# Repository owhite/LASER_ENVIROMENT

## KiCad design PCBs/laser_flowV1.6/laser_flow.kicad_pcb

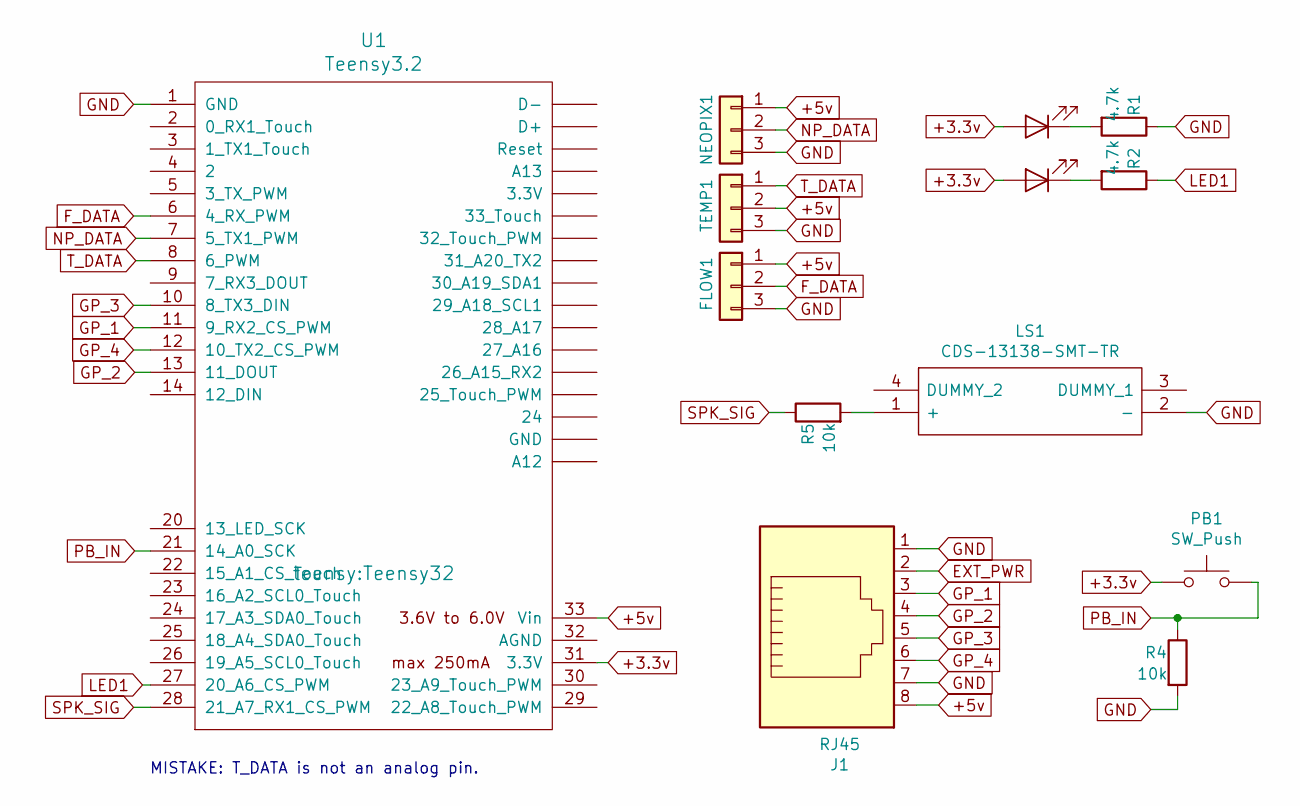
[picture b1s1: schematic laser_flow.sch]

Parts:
D1, D2: LED; LED_0805_2012Metric
FLOW1: Conn_01x03; PinHeader_1x03_P2.54mm_Vertical
J1: RJ45; my_RJ45_Amphenol
LS1: CDS-13138-SMT-TR; CDS13138SMTTR; Manufacturer_Part_Number CDS-13138-SMT-TR
NEOPIX1: Conn_01x03; PinHeader_1x03_P2.54mm_Vertical
PB1: SW_Push; SW_SPST_TL3342
R1, R2: 4.7k; R_0805_2012Metric
R4, R5: 10k; R_0805_2012Metric
TEMP1: Conn_01x03; PinHeader_1x03_P2.54mm_Vertical
U1: Teensy3.2; Teensy32

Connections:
+3.3v: D1.2 (A), D2.2 (A), PB1.1, U1.31 (3.3V)
+5v: FLOW1.1, J1.8, NEOPIX1.1, TEMP1.2, U1.33 (Vin)
EXT_PWR: J1.2
F_DATA: FLOW1.2, U1.6 (4_RX_PWM)
GND: FLOW1.3, J1.1, J1.7, LS1.2 (-), NEOPIX1.3, R1.1, R4.2, TEMP1.3, U1.1 (GND)
GP_1: J1.3, U1.11 (9_RX2_CS_PWM)
GP_2: J1.4, U1.13 (11_DOUT)
GP_3: J1.5, U1.10 (8_TX3_DIN)
GP_4: J1.6, U1.12 (10_TX2_CS_PWM)
LED1: R2.1, U1.27 (20_A6_CS_PWM)
NP_DATA: NEOPIX1.2, U1.7 (5_TX1_PWM)
unnamed: D1.1 (K), R1.2
unnamed: D2.1 (K), R2.2
unnamed: LS1.1 (+), R5.2
PB_IN: PB1.2, R4.1, U1.21 (14_A0_SCK)
SPK_SIG: R5.1, U1.28 (21_A7_RX1_CS_PWM)
T_DATA: TEMP1.1, U1.8 (6_PWM)

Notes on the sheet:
MISTAKE: T_DATA is not an analog pin.

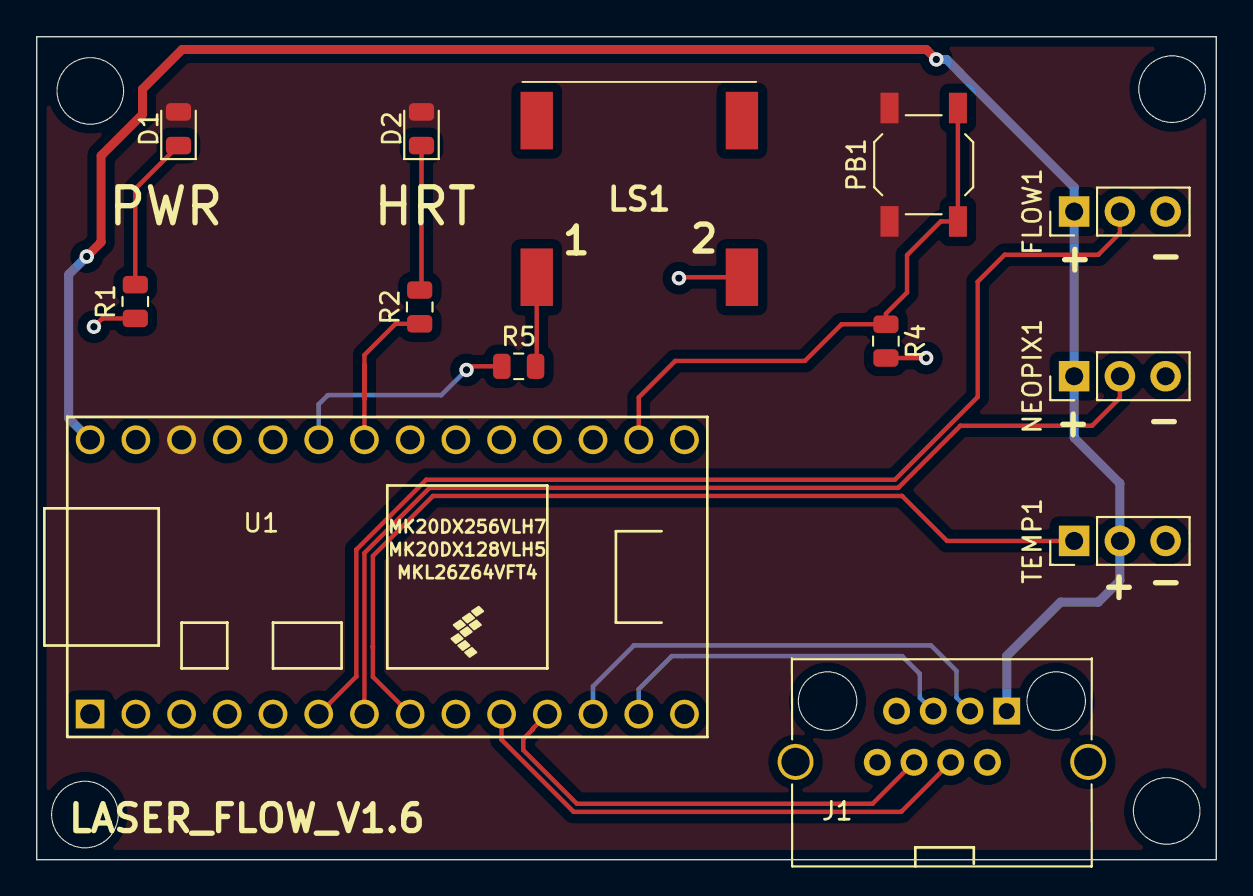
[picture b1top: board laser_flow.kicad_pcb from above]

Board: 2 copper layers, 65.5 x 45.7 mm, 13 parts (0 on the bottom side), 16 nets.

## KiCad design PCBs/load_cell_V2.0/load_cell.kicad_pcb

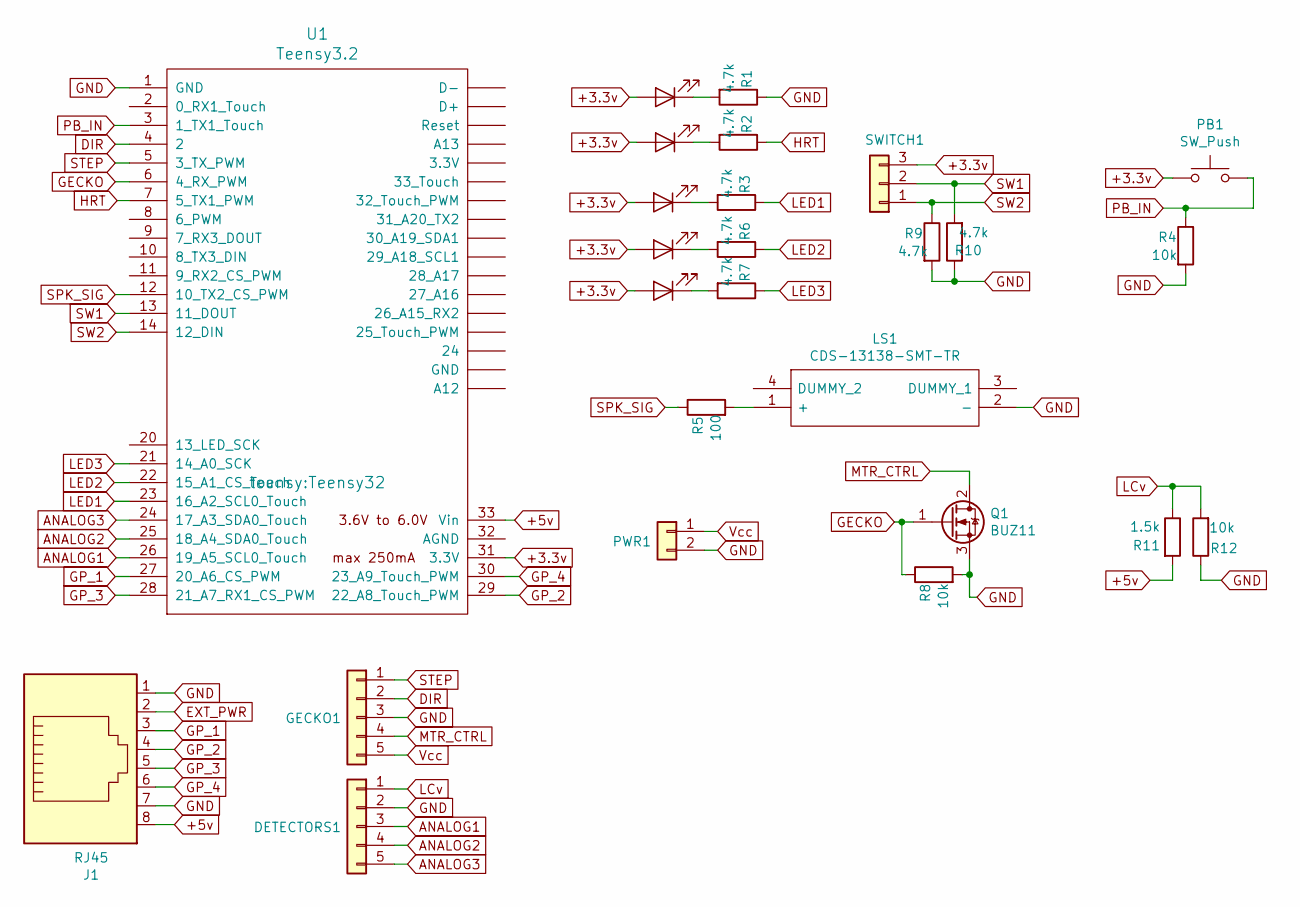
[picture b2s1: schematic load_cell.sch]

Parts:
D1, D2, D3, D4, D5: LED; LED_0805_2012Metric
DETECTORS1: Conn_01x05; PinHeader_1x05_P2.54mm_Vertical
GECKO1: Conn_01x05; PinHeader_1x05_P2.54mm_Vertical
J1: RJ45; my_RJ45_Amphenol
LS1: CDS-13138-SMT-TR; CDS13138SMTTR; Manufacturer_Part_Number CDS-13138-SMT-TR
PB1: SW_Push; SW_SPST_TL3342
PWR1: Conn_01x02; PinHeader_1x02_P2.54mm_Vertical
Q1: BUZ11; TO-220-3_Vertical
R1, R2, R3, R6, R7, R9, R10: 4.7k; R_0805_2012Metric
R4, R8, R12: 10k; R_0805_2012Metric
R5: 100; R_0805_2012Metric
R11: 1.5k; R_0805_2012Metric
SWITCH1: Conn_01x03; PinHeader_1x03_P2.54mm_Vertical
U1: Teensy3.2; Teensy32

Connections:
+3.3v: D1.2 (A), D2.2 (A), D3.2 (A), D4.2 (A), D5.2 (A), PB1.1, SWITCH1.3, U1.31 (3.3V)
+5v: J1.8, R11.2, U1.33 (Vin)
ANALOG1: DETECTORS1.3, U1.26 (19_A5_SCL0_Touch)
ANALOG2: DETECTORS1.4, U1.25 (18_A4_SDA0_Touch)
ANALOG3: DETECTORS1.5, U1.24 (17_A3_SDA0_Touch)
DIR: GECKO1.2, U1.4 (2)
EXT_PWR: J1.2
GECKO: Q1.1 (G), R8.1, U1.6 (4_RX_PWM)
GND: DETECTORS1.2, GECKO1.3, J1.1, J1.7, LS1.2 (-), PWR1.2, Q1.3 (S), R1.1, R4.2, R8.2, R9.2, R10.1, R12.1, U1.1 (GND)
GP_1: J1.3, U1.27 (20_A6_CS_PWM)
GP_2: J1.4, U1.29 (22_A8_Touch_PWM)
GP_3: J1.5, U1.28 (21_A7_RX1_CS_PWM)
GP_4: J1.6, U1.30 (23_A9_Touch_PWM)
HRT: R2.1, U1.7 (5_TX1_PWM)
LCv: DETECTORS1.1, R11.1, R12.2
LED1: R3.1, U1.23 (16_A2_SCL0_Touch)
LED2: R6.1, U1.22 (15_A1_CS_Touch)
LED3: R7.1, U1.21 (14_A0_SCK)
MTR_CTRL: GECKO1.4, Q1.2 (D)
unnamed: D1.1 (K), R7.2
unnamed: D2.1 (K), R6.2
unnamed: D3.1 (K), R3.2
unnamed: D4.1 (K), R2.2
unnamed: D5.1 (K), R1.2
unnamed: LS1.1 (+), R5.2
PB_IN: PB1.2, R4.1, U1.3 (1_TX1_Touch)
SPK_SIG: R5.1, U1.12 (10_TX2_CS_PWM)
STEP: GECKO1.1, U1.5 (3_TX_PWM)
SW1: R10.2, SWITCH1.2, U1.13 (11_DOUT)
SW2: R9.1, SWITCH1.1, U1.14 (12_DIN)
Vcc: GECKO1.5, PWR1.1

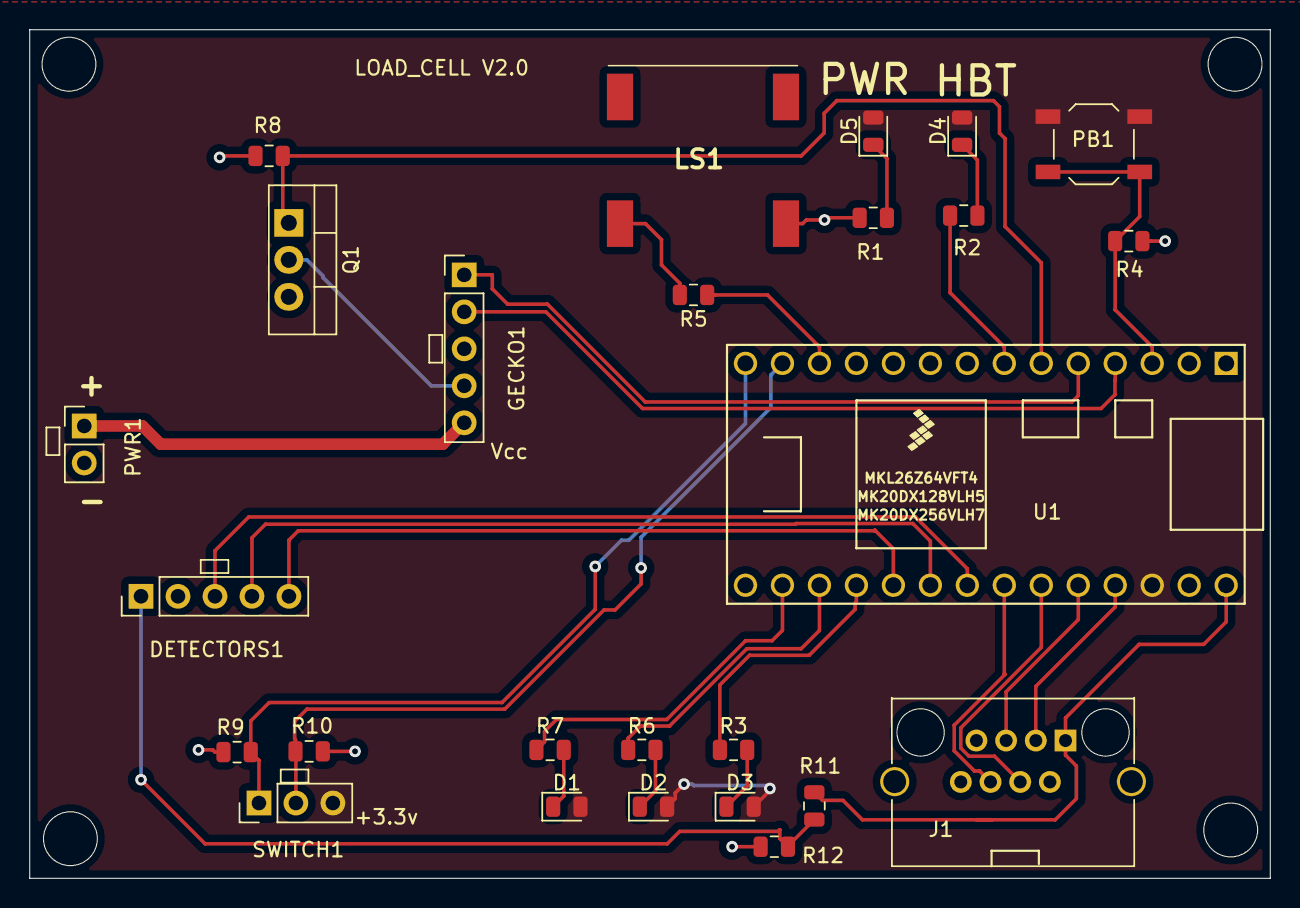
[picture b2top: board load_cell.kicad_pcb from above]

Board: 2 copper layers, 85.2 x 58.3 mm, 26 parts (0 on the bottom side), 30 nets.

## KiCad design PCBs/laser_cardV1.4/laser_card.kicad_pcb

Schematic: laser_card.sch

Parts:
100_1, 100_2, 100_3, 100_4: C; C_0805_2012Metric
+5_JP1, +5_JP2: SolderJumper_2_Open; SolderJumper-2_P1.3mm_Open_RoundedPad1.0x1.5mm
+5v_SW1: TestPoint; TestPoint_THTPad_2.0x2.0mm_Drill1.0mm
ANLG_FOR1: TestPoint; TestPoint_THTPad_2.0x2.0mm_Drill1.0mm
ANLG_REFL1: TestPoint; TestPoint_THTPad_2.0x2.0mm_Drill1.0mm
C1, C2: 10u; CP_Radial_D6.3mm_P2.50mm
D1, D2: LED; LED_0805_2012Metric
D4: SM4003; D_SOD-123F
D5, D6: BZT52Bxx; D_SOD-123
DB25: DB25_Female_MountingHoles; DSUB-25_Female_Vertical_P2.77x2.84mm_MountingHoles
E-STOP1, E-STOP2, E-STOP3: Conn_01x02; PinHeader_1x02_P2.54mm_Vertical
ENC-X1: RJ45_Shielded; my_RJ45_Amphenol
ENC-Y1: RJ45_Shielded; my_RJ45_Amphenol
ENC-Z1: RJ45_Shielded; my_RJ45_Amphenol
EXT_PWR1: Conn_01x02; PinHeader_1x02_P2.54mm_Vertical
GECKO-X1: molex; PinHeader_1x08_P2.54mm_Vertical
GECKO-Y1: molex; PinHeader_1x08_P2.54mm_Vertical
GECKO-Z1: molex; PinHeader_1x08_P2.54mm_Vertical
GND1: TestPoint; TestPoint_THTPad_2.0x2.0mm_Drill1.0mm
GP1, GP2, GP3, GP4, GP5: RJ45_Shielded; my_RJ45_Amphenol
IDC1, IDC2: Conn_02x25_Odd_Even; IDC-Header_2x25_P2.54mm_Vertical
JP1, JP2, JP3, JP4, JP5: SolderJumper_2_Open; SolderJumper-2_P1.3mm_Open_RoundedPad1.0x1.5mm
K1: G6E; Relay_SPDT_Omron_G6E
LASER_ENABLE1: TestPoint; TestPoint_THTPad_2.0x2.0mm_Drill1.0mm
PWM_EXT1: TestPoint; TestPoint_THTPad_2.0x2.0mm_Drill1.0mm
PWM_OUT1: TestPoint; TestPoint_THTPad_1.5x1.5mm_Drill0.7mm
PWM_SEL1: Conn_01x03; PinHeader_1x03_P2.54mm_Vertical
Q1: MBT2222ADW1T1; SOT-363_SC-70-6
R1, R2: 10k; R_0805_2012Metric
R3, R4, R5, R12: 1k; R_0805_2012Metric
R10, R11, R13, R14, R15, R16, R17, R18, R19, R20: 2.7k; R_0805_2012Metric
U1: SN75172_LINE_DRIVER; SOIC-20W_7.5x12.8mm_P1.27mm
U2, U3: SN75173_differential_line_receiver; SOIC-16_4.55x10.3mm_P1.27mm
U4: 74LS14; SOIC-14_3.9x8.7mm_P1.27mm
U5: my_buck_boost-Regulator_Switching; my_buck_boost

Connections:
+5v: 100_1.1, 100_2.1, 100_3.1, 100_4.2, +5_JP1.2, +5_JP2.2, C2.1, D6.1 (K), GP1.8, GP2.8, GP3.8, GP4.8, GP5.8, K1.1, K1.12, R1.1, R11.2, R14.1, R16.1, R18.1, R20.1, U1.5 (EN), U1.9 (DIN2), U1.11 (DIN3), U1.19 (DIN4), U1.20 (VCC), U2.4 (G), U2.6 (2A), U2.7 (2B), U2.9 (3B), U2.10 (3A), U2.14 (4A), U2.15 (4B), U2.16 (VDD), U3.4 (G), U3.16 (VDD), U4.5, U4.9, U4.11, U4.13, U4.14 (VCC), U5.7 (Reg_out), U5.8 (Reg_out)
+5v_SW: +5v_SW1.1, C1.1, GECKO-X1.1, GECKO-Y1.1, GECKO-Z1.1, K1.7, R2.1, R3.1
DB1: ANLG_FOR1.1, DB25.1
DB2: ANLG_REFL1.1, DB25.2
DB3: DB25.3, Q1.6 (C1)
DB4: DB25.4, R10.2, U2.2 (1A)
DB7: DB25.7, U1.2 (DOUT1+)
DB8: DB25.8, R19.1, U3.14 (4A)
DB9: DB25.9, R17.1, U3.10 (3A)
DB10: DB25.10, R13.1, U3.2 (1A)
DB11: DB25.11, R15.1, U3.6 (2A)
DB12: DB25.12
DB14: DB25.14, Q1.1 (E1)
DB17: DB25.17, R11.1, U2.1 (1B)
DB20: DB25.20, U1.4 (DOUT1-)
DB21: DB25.21, R20.2, U3.15 (4B)
DB22: DB25.22, R18.2, U3.9 (3B)
DB23: DB25.23, R14.2, U3.1 (1B)
DB24: DB25.24, R16.2, U3.7 (2B)
DIGITAL_FORWARD: IDC2.15, U3.11 (3Y)
DIGITAL_REFLECTED: IDC2.19, U3.13 (4Y)
DIG_0: IDC2.45
DIG_1: IDC2.43
DIG_2: IDC2.41
DIG_3: IDC2.39
DIG_4: IDC2.37
DIG_5: IDC2.35
DIG_6: IDC2.33
DIG_7: IDC2.31
DUTY_CYCLE: IDC2.13, U3.3 (1Y)
E-STOP: E-STOP1.1, IDC1.47
EXT_PWR: EXT_PWR1.2, JP1.2, JP2.2, JP3.2, JP4.2, JP5.2, U5.3 (IN_+), U5.4 (IN_+)
GND: 100_1.2, 100_2.2, 100_3.2, 100_4.1, C1.2, C2.2, D1.1 (K), D2.1 (K), D4.2 (A), D5.2 (A), DB25.0 (PAD), DB25.15, DB25.16, E-STOP3.2, ENC-X1.SH, ENC-Y1.SH, ENC-Z1.SH, EXT_PWR1.1, GND1.1, GP1.1, GP1.7, GP1.SH, GP2.1, GP2.7, GP2.SH, GP3.1, GP3.7, GP3.SH, GP4.1, GP4.7, GP4.SH, GP5.1, GP5.7, GP5.SH, IDC1.2, IDC1.4, IDC1.6, IDC1.8, IDC1.10, IDC1.12, IDC1.14, IDC1.16, IDC1.18, IDC1.20, IDC1.22, IDC1.24, IDC1.26, IDC1.28, IDC1.30, IDC1.32, IDC1.34, IDC1.36, IDC1.38, IDC1.40, IDC1.42, IDC1.44, IDC1.46, IDC1.48, IDC1.50, IDC2.2, IDC2.4, IDC2.6, IDC2.8, IDC2.10, IDC2.12, IDC2.14, IDC2.16, IDC2.18, IDC2.20, IDC2.22, IDC2.24, IDC2.26, IDC2.28, IDC2.30, IDC2.32, IDC2.34, IDC2.36, IDC2.38, IDC2.40, IDC2.42, IDC2.44, IDC2.46, IDC2.48, IDC2.50, Q1.4 (E2), R3.2, R10.1, R13.2, R15.2, R17.2, R19.2, U1.10 (GND), U1.15 (~EN), U2.8 (GND), U2.12 (~G), U3.8 (GND), U3.12 (~G), U4.7 (GND), U5.1 (IN_-), U5.2 (IN_-), U5.5 (Reg_GND), U5.6 (Reg_GND)
GP1_1: GP2.3, IDC1.3
GP1_2: GP2.4, IDC1.9
GP1_3: GP2.5, IDC1.5
GP1_4: GP2.6, IDC1.7
GP2_1: GP1.3, IDC1.11
GP2_2: GP1.4, IDC1.17
GP2_3: GP1.5, IDC1.13
GP2_4: GP1.6, IDC1.15
GP3_1: GP3.3, IDC1.19
GP3_2: GP3.4, IDC1.25
GP3_3: GP3.5, IDC1.21
GP3_4: GP3.6, IDC1.23
GP4_1: GP4.3, IDC1.27
GP4_2: GP4.4, IDC1.33
GP4_3: GP4.5, IDC1.29
GP4_4: GP4.6, IDC1.31
GP5_1: GP5.3, IDC1.35
GP5_2: GP5.4, IDC1.41
GP5_3: GP5.5, IDC1.37
GP5_4: GP5.6, IDC1.39
GX_DIR: GECKO-X1.3, IDC2.21
GX_ENC+: ENC-X1.8, GECKO-X1.6, GECKO-X1.8
GX_ENC-: ENC-X1.7, GECKO-X1.7
GX_PHA: ENC-X1.6, GECKO-X1.5
GX_PHB: ENC-X1.5, GECKO-X1.4
GX_STP: GECKO-X1.2, IDC2.23
GY_DIR: GECKO-Y1.3, IDC2.25
GY_ENC+: ENC-Y1.8, GECKO-Y1.6, GECKO-Y1.8
GY_ENC-: ENC-Y1.7, GECKO-Y1.7
GY_PHA: ENC-Y1.6, GECKO-Y1.5
GY_PHB: ENC-Y1.5, GECKO-Y1.4
GY_STP: GECKO-Y1.2, IDC2.27
GZ_DIR: GECKO-Z1.3, IDC1.45
GZ_ENC+: ENC-Z1.8, GECKO-Z1.6, GECKO-Z1.8
GZ_ENC-: ENC-Z1.7, GECKO-Z1.7
GZ_PHA: ENC-Z1.6, GECKO-Z1.5
GZ_PHB: ENC-Z1.5, GECKO-Z1.4
GZ_STP: GECKO-Z1.2, IDC1.43
LASER_ENABLE: LASER_ENABLE1.1, R5.2, U4.2
LASER_PWM: PWM_OUT1.1, PWM_SEL1.2, U1.1 (DIN1)
unnamed: +5_JP1.1, IDC1.49
unnamed: +5_JP2.1, IDC2.49
unnamed: D1.2 (A), R1.2
unnamed: D2.2 (A), R2.2
unnamed: D4.1 (K), D5.1 (K), R5.1, R12.2
unnamed: D6.2 (A), K1.6, Q1.3 (C2)
unnamed: E-STOP1.2, E-STOP2.1
unnamed: E-STOP2.2, E-STOP3.1
unnamed: GP1.2, JP2.1
unnamed: GP2.2, JP1.1
unnamed: GP3.2, JP3.1
unnamed: GP4.2, JP4.1
unnamed: GP5.2, JP5.1
unnamed: IDC2.1, U4.1
unnamed: IDC2.3, U4.3
unnamed: Q1.2 (B1), R12.1
unnamed: Q1.5 (B2), R4.2
OVER_TEMP: IDC1.1, U2.3 (1Y)
PWM_EXT: PWM_EXT1.1, PWM_SEL1.3
PWM_INTERNAL: IDC2.11, PWM_SEL1.1
RELAY: R4.1, U4.4
VSWR: IDC2.17, U3.5 (2Y)

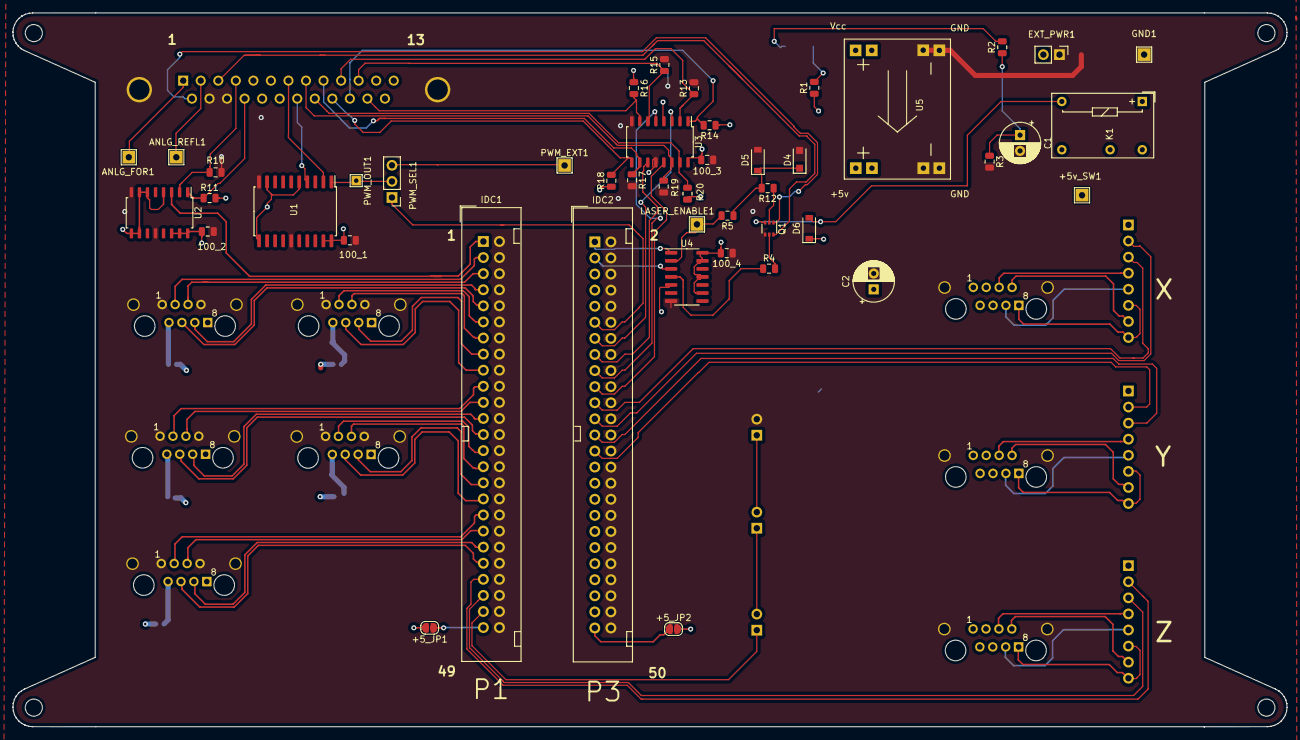
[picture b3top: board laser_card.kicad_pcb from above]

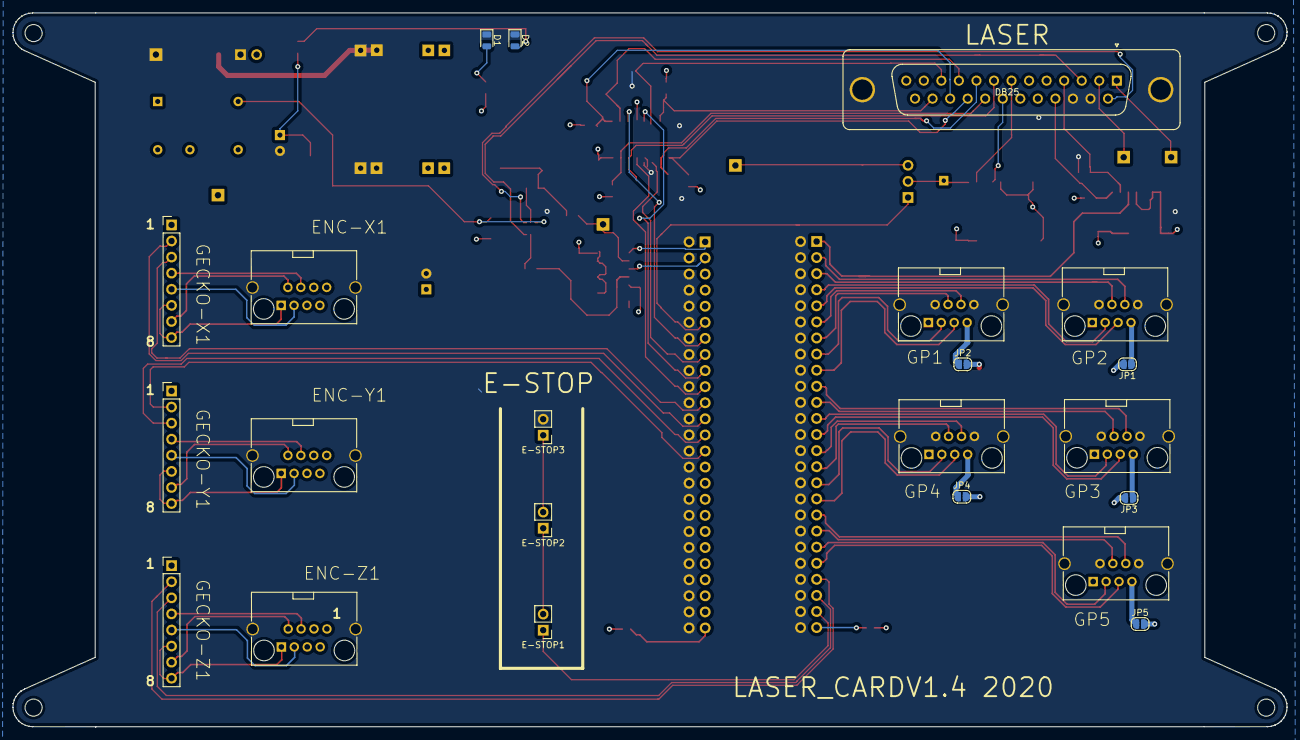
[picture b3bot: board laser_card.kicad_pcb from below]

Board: 4 copper layers, 201.2 x 112.7 mm, 67 parts (22 on the bottom side), 86 nets.

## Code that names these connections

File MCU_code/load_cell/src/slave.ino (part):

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#define SPKR_PIN   10
#define PB_PIN     1

#define LED1       14 // indicators of load cell status
#define LED2       15
#define LED3       16

#define LC_PIN1    19 // input from the load cells
#define LC_PIN2    18
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  pinMode(STEP_PIN, OUTPUT);
  pinMode(DIR_PIN, OUTPUT);
  pinMode(LED_PIN, OUTPUT);
  pinMode(LED1, OUTPUT);
  pinMode(LED2, OUTPUT);
  pinMode(LED3, OUTPUT);

  digitalWrite(STEP_PIN, HIGH);
  digitalWrite(DIR_PIN, HIGH);
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
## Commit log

2018-07-03 2018 update
2020-08-31 removed a bunch of files
2020-08-31 Code, MCU, files from latest build
2020-08-31 added PCBs
2020-08-31 Rename README.mk to README.md
2020-08-31 added pics
2020-08-31 removed a folder
2020-08-31 add CAD file
2020-08-31 add rhino3d_macros
2020-08-31 deleted crap
2020-08-31 add relay_driver
2020-08-31 moved files around
2020-08-31 added laser_flow
2022-07-01 fixed mm/inches
2024-11-26 minor edit
2024-11-26 fixed G20 and G21 for metric docs
